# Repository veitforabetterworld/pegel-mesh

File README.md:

# pegel-mesh

Wasserstände von entfernten Pegeln per Funk ins Netz, ohne Mobilfunk. Ein Sender am Fluss liest die Pegelsonde (RS485) und funkt über [MeshCore](https://github.com/meshcore-dev/MeshCore) (868 MHz) zu einem Empfänger mit WLAN, der die Werte an die **hochwasserdienst**-API schickt. Der Sender läuft mit Solarpanel und Akku.

Zwei Trägerplatinen, eine Firmware (gleiche XIAO-Pins; die Firmware erkennt den Akku selbst):

| Platine | Akku | Versorgung |
|---|---|---|
| [`pegel-sender-12v`](hardware/pegel-sender-12v/README.md) (100 × 70 mm) | LiFePO4 oder ohne | Solarpanel 12-V-Klasse oder 12-V-Netzteil |
| [`pegel-sender-5v`](hardware/pegel-sender-5v/README.md) (58 × 46 mm) | Li-Ionen oder ohne | USB-C-Netzteil oder USB-C-Solarpanel (5 V), Heizung 1,7 W |
| [`pegel-stapel`](hardware/pegel-stapel/README.md) (Stapel) | wie oben | RS485-Platine auf Ladeplatine 5 V (beide 21 × 17,8 mm, wie der XIAO) oder 12 V (100 × 70 mm); Thermolader für 12-V-Netzteil und 12-V-Solar im Entwurf, noch unverdrahtet |

## Platine (12 V)

Die SMD-Teile bestückt JLCPCB (Dateien in [`hardware/pegel-sender-12v/fab/`](hardware/pegel-sender-12v/fab/)). Selbst löten:

| Teil | Wert | Beispiel |
|---|---|---|
| SOLAR/12V, AKKU | Schraubklemme 2-pol., Raster 5,08 mm | Phoenix MKDS 1,5/2-5,08 |
| SONDE, HEIZ/NTC | Schraubklemme 4-pol., Raster 5,08 mm | Phoenix MKDS 1,5/4-5,08 |
| L1 | Spule 15 µH, ≥ 0,9 A, radial Ø 7 mm, Raster 3 mm | Bourns RLB0712-150KL |
| L2 | Spule 10 µH, ≥ 0,5 A, radial Ø 7 mm, Raster 3 mm | Bourns RLB0712-100KL |
| C22 | Elko 220 µF 16 V, Polymer oder Low-ESR, Ø 8 mm, Raster 3,5 mm | Panasonic 16SEPF220M |
| C23 | Elko 220 µF 50 V, Low-ESR, Ø 10 mm, Raster 5 mm | Panasonic EEU-FR1H221 |
| XIAO | 2× Buchsenleiste 1×7, 2,54 mm | |
| NETZTEIL | Stiftleiste 1×2, 2,54 mm + Steckbrücke | |

Elkos: Plus an das Pad mit „+“.

Schaltplan: [`hardware/pegel-sender-12v/preview/`](hardware/pegel-sender-12v/preview/) (Blockschaltbild und ein Blatt je Funktionsblock), Technik in [`hardware/pegel-sender-12v/`](hardware/pegel-sender-12v/README.md).

## Anschlüsse

| Klemme | Was |
|---|---|
| **SOLAR/12V** | 12-V-Solarpanel (Leerlauf ≤ 25 V; 10 W Flachland, 30 W Mittelgebirge) **oder** 12-V-Netzteil |
| **AKKU** | LiFePO4, **1 Zelle** (3,2 V), z. B. 2–3 × 6 Ah parallel. Rückstellende Sicherung **RUEF300** (Littelfuse PolySwitch, hält 3 A, löst bei 6 A aus) im Pluskabel, direkt am Akku-Pluspol |
| **HEIZ/NTC** | H+ / H−: Heizwiderstand 68 Ω 10 W; NTC / NTC: Fühler 10 kΩ B3950, **auf den Akku** kleben |
| **SONDE** | V+ rot, V− schwarz, A weiß, B blau. RS485 Modbus RTU, 9600 8N1, Adresse 1, 12 V ≤ 30 mA |
| **NETZTEIL** (Brücke) | gesteckt bei Netzteil, offen bei Solarpanel |

Ohne NTC lädt der Sender nie (gilt als Frost). XIAO nRF52840 mit Wio-SX1262 aufstecken, USB zum Platinenrand („USB ->“); den BAT-Anschluss am XIAO nicht benutzen.

## Installation

Voraussetzungen: Git, Python 3.12+, USB-Treiber für die XIAO-Boards.

```bash
git clone https://github.com/veitforabetterworld/pegel-mesh.git
```

```bash
cd pegel-mesh && git submodule update --init
```

```bash
python3 -m pip install platformio cryptography
```

```bash
python3 tools/genkeys.py
```

`genkeys.py` legt `secrets/` an (nicht im Repo, sicher aufbewahren). Dort von Hand ausfüllen: **`secrets/receiver_wifi.h`** mit WLAN, API-Key (hochwasserdienst: Admin > API-Keys) und Name/Koordinaten der Stationen. Weitere Sender: `python3 tools/genkeys.py A B C`.

Flashen (Port anpassen, unter Windows z. B. `COM5`):

```bash
python3 tools/pio.py run -e pegel_sender_a -t upload --upload-port /dev/ttyACM0
```

| Umgebung | Gerät |
|---|---|
| `pegel_sender_a` | Sender, Messung jede Minute |
| `pegel_sender_b` | Sender, Messung alle 5 min |
| `pegel_receiver` | Empfänger, XIAO ESP32-S3 + Wio-SX1262 |

Immer `tools/pio.py` statt `pio` aufrufen; es hängt `pegel.ini` in das MeshCore-Submodul ein.

## Funkausfall und Nachsenden

Der Sender hält jede Messung, bis der Empfänger sie quittiert: 6144 Messungen, bei Sender A gut 4 Tage, bei Sender B gut 3 Wochen. Ist der Puffer voll, fällt die älteste Messung heraus; nach 30 Tagen verfällt eine Messung ebenfalls. Bei gestörter Verbindung stehen die Messungen zusätzlich im Flash und überstehen Stromausfall und Neustart; die Uhrzeit dafür kommt mit jeder Quittung vom Empfänger.

- Im Messtakt geht immer ein Block mit den neuesten Messungen raus (bis 75 je Paket). Bleibt die Quittung aus, versucht es der Sender erst im nächsten Messtakt wieder.
- Kam die Quittung, folgt der restliche Stau Block für Block, neueste zuerst, solange das Sendebudget von 1 % je Stunde reicht (MeshCore setzt es durch). Ein Tag Ausfall von Sender A ist so in knapp einer Stunde nachgeholt.
- Daten und Quittungen laufen nur auf dem bekannten Pfad oder ohne Hops, nie geflutet.

Fängt der Zähler eines Senders neu an (Tausch, Neuaufsetzen), übernimmt der Empfänger den neuen Stand nach etwa 30 Blöcken; sofort geht es am Empfänger über USB-Serial mit `creset <Sender>`, z. B. `creset A`.

## Langzeitbetrieb

Die Firmware ist für den Betrieb über viele Jahrzehnte ausgelegt (Watchdog, Überlauf- und Verschleißschutz). Der Empfänger nimmt die Uhrzeit vom Server. Zwischen den Messungen schlafen Funkchip und CPU. Bei gestörter Verbindung schreibt der Sender jede Messung mit Uhrzeit in den Flash: nach einem Stromausfall sendet er sie mit dem richtigen Zeitstempel nach.

Notfallwege testen: Builds `pegel_sender_a_test` und `pegel_receiver_test` (Serial-Befehle in `firmware/sender/main.cpp` bzw. `firmware/receiver/main.cpp`, `PEGEL_TEST_CMDS`).

## GPS-Tracker

Der Empfänger ist zugleich Gateway für GPS-Tracker: XIAO nRF54LM20A Sense + Wio-SX1262 + L76K-GNSS-Modul (Seeed 109100021). Der Tracker schläft zwischen den Ortungen in System OFF, meldet Position und Akkustand verschlüsselt über MeshCore, speichert nicht quittierte Meldungen zwischen und reicht sie nach. Bei eingeschaltetem Bewegungsalarm weckt ihn der Bewegungssensor. Der Empfänger lädt die Meldungen zu [tracker.plenivo.de](https://tracker.plenivo.de) hoch und gibt dem Tracker dessen Einstellungen (Intervall, Alarm) mit. Firmware in [`firmware/tracker/`](firmware/tracker/), Paketformat in [`firmware/common/tracker_packet.h`](firmware/common/tracker_packet.h).

Schlüssel für einen neuen Tracker (hier `T1`), danach den Empfänger neu flashen:

```bash
python3 tools/genkeys.py --tracker T1
```

In `secrets/receiver_wifi.h` `TRACKER_API_URL` (`https://tracker.plenivo.de/api`) und je Tracker den API-Key aus dem Tracker-Dialog der Webseite eintragen. Ohne URL gibt der Empfänger die Meldungen nur auf Serial aus; Einstellungen lassen sich dann mit `tset <tracker> <intervall 0..3> <alarm 0..3> <alarmintervall 0..3>` auf Serial setzen.

Der nRF54LM20A wird von MeshCore noch nicht offiziell unterstützt; der Tracker baut gegen das Submodul `MeshCore-nrf54` (MeshCore-PR #3530). `tools/pio.py` wählt es für alle Umgebungen `tracker_*` und hängt `tracker.ini` ein.

```bash
python3 tools/pio.py run -e tracker_t1 -t upload
```

Ein neues Board ist ab Werk gesperrt (APPROTECT): einmal mit OpenOCD über den CTRL-AP löschen und dann `-t bootloader` (Bootloader, SoftDevice, Firmware) flashen; danach reicht `-t upload`. Die USB-Seriell-Brücke des Boards bleibt nach System OFF oft hängen; das Log liegt deshalb zusätzlich im RAM und lässt sich per SWD lesen (weckt den Tracker dabei auf):

```bash
bash tools/tracker_log.sh
```

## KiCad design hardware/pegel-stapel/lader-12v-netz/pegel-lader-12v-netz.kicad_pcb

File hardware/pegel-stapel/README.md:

# pegel-stapel: Ladeplatine + RS485-Platine zum Stapeln

Die Sender-Elektronik in zwei Platinen, gestapelt wie der XIAO selbst. Unten liegt eine Ladeplatine, wahlweise für 5 V oder 12 V. Darüber sitzt die RS485-Platine, ganz oben XIAO nRF52840 + Wio-SX1262. Alle Platinen haben die XIAO-Leisten an derselben Stelle, und die Signale laufen durch die Stapelbuchsen. Firmware: die normalen Umgebungen `pegel_sender_a`/`_b`; den Akku (Li-Ionen oder LiFePO4) erkennt sie selbst, von der Temperaturregelung weiß sie nichts.

| Platine | Inhalt | Größe |
|---|---|---|
| [`rs485/`](rs485/) | 12 V für die Sonde (TPS61040, ausgelegt auf 13 mA), RS485 (SP3485), Lötstellen J3 **A, B, GND, 12V**, durchkontaktiert im 2,54-mm-Raster | 20,955 × 17,78 mm (Umriss des XIAO) |
| [`lader-5v/`](lader-5v/) | **Thermolader 5 V:** 5-V-Eingang J1, NTC J4, LM393: unter ~2,5 °C Heizung 5 × 300 Ω (0,42 W), über ~42 °C Laden aus, dazwischen Laden über den XIAO | 20,955 × 17,78 mm (Umriss des XIAO) |
| [`lader-12v-netz/`](lader-12v-netz/) | **Thermolader 12 V Netzteil** (9–15 V): TPS54331 auf 4,88 V, dahinter wie 5 V. Verdrahtet, GND und Versorgung als Flächen | 21,975 × 17,78 mm |
| [`lader-12v-solar/`](lader-12v-solar/) | **Thermolader 12 V Solar** (36 Zellen, Leerlauf bis 25 V): TPS5430 auf 4,92 V mit Panelregelung, dahinter wie 5 V. Noch nicht verdrahtet | 31,455 × 17,78 mm |
| [`lader-12v/`](lader-12v/) | Solar/12 V, LiFePO4-Lader, Frostschutz, Schaltung, Klemmen und Bohrungen wie `pegel-sender-12v` (gleiches Gehäuse) | 100 × 70 mm |

| | |
|---|---|
|  |  |

## Stapel

- **Stapelmaß:** Die XIAO-Leisten liegen auf allen Platinen gleich, 15,24 mm auseinander, USB-C nach rechts ([`tools/stack.py`](tools/stack.py)). RS485-Platine und Thermolader haben den Umriss des XIAO und keine Bohrungen, das Langloch-Symbol unten zeigt die USB-C-Kante. Die 12-V-Ladeplatine hat nur die vier Gehäusebohrungen in den Ecken.
- **Ladeplatine:** zwei Buchsenleisten 1×7 (8,5 mm).
- **RS485-Platine:** zwei Stapel-Buchsenleisten 1×7 mit langen Stiften. Die Stifte gehen nach unten in die Ladeplatine, der XIAO steckt oben.
- **5-V-Ladeplatine (Thermolader 5 V):** nur so groß wie der XIAO, ohne Bohrungen; sie hängt an den beiden Leisten. Das Langloch-Symbol auf der Unterseite zeigt, an welcher Kante die USB-C-Buchse des XIAO sitzt.
- **Halt:** Die Platinen halten nur an den Leisten, Abstandsbolzen gibt es nicht.
- **Signale zwischen den Platinen:** nur über die 14 Pins der XIAO-Leisten, nämlich D0 (Sonde ein), D6/D7 (RS485), 3V3, GND und 5V. Keine Drähte.
- **Frostschutz in Hardware, beide Ladeplatinen:** ein NTC 10 kΩ B3950 am Akku.
  - 5 V: Eine Hälfte des LM393 trennt unter ~2,5 °C den Lader des XIAO vom 5-V-Eingang (Q2) und heizt, bis der Akku wieder ~4,6 °C hat. Die andere trennt über ~42 °C (ungünstigste Toleranzen 39,2–44,8 °C) bis ~37 °C (Q3). Ohne NTC: kein Laden, Heizung an. NTC-Kurzschluss: kein Laden, Heizung aus.
  - 12 V: Ein LM324 regelt wie bei `pegel-sender-12v`.

## Versorgung

- **Sonde:** Der 12-V-Wandler läuft aus dem **3V3-Pin** des XIAO, nicht aus dem Akku. Bei 5 V liefert der Regler des XIAO die 3,3 V (SGM2040: 280 mA garantiert, höchstens 10 µF am Ausgang empfohlen). Bei 12 V speist die Ladeplatine den 3V3-Pin über D10 direkt aus dem LiFePO4-Akku. Die Sonde braucht 13 mA bei 12 V, das sind ~61 mA aus 3,3 V und nur während der Messung.
- **Einschalten der Sonde:** Q7 schaltet Wandler und SP3485 gemeinsam. C9/C11 rampen die 3,3 V, C10/D7/R19 die 12 V (~65 ms, zählt zur Vorlaufzeit von 2 s). Gerechnet mit den ungünstigsten Grenzen bleibt 3V3 bis 100 µF in der Sonde über 3,1 V, bei 220 µF 2,6 V. Am ersten Aufbau mit echter Sonde messen.
- **Sondenkabel:** Eine 1 hält auf dem Bus nur die Vorspannung R17/R18 (1 kΩ). Bei 9600 Bd reicht das rechnerisch für ~180 m (120 pF/m). Kein Abschlusswiderstand nötig.
- **5 V:** Li-Ionen-Akku an die BAT-Pads des XIAO und unter die Ladeplatine kleben, mit den Heizwiderständen darüber. Der NTC kommt an den Akku. J4 (NTC) und J1 (5 V) sind Lötpads auf der Unterseite. Stiftenden kürzen und samt Pads gegen den Akku isolieren.
- **Wärme:** nachgerechnet in [`verify/report/thermal.md`](verify/report/thermal.md) (700 mAh, 3 cm Styropor). Die Heizung reicht bis etwa −25 °C, bei 4,5 V bis etwa −19 °C. **Fällt der NTC ab, heizt sie dauernd:** der Akku kommt bei 20 °C Außenluft auf ~50 °C, bei 35 °C auf ~64 °C (61–69 °C); über seine 60 °C kommt er ab ~31 °C Außenluft (ungünstig ab 26 °C). Die Hitzeabschaltung verhindert das nicht, sie schaltet nur das Laden. NTC deshalb sicher am Akku befestigen, neben der Platine, nie zwischen Platine und Akku: dort lädt es bei teils gefrorenem Akku. Ab ~35 °C Außenluft lädt es nur zeitweise, über ~40 °C gar nicht.
- **Kupfer (5 V):** GND beidseitig als Fläche ohne GND-Bahnen, V5, HEAT_N und XIAO_5V als Flächen, Signale 0,3 mm, übrige Versorgung 0,6 mm, Abstand ≥ 0,2 mm. Nach Änderungen in KiCad Flächen neu füllen (Taste B).
- **Kupfer (RS485):** GND beidseitig als Fläche, V3_SW und Schaltknoten als Flächen, Signale 0,3 mm, 12 V und XIAO-3V3 im Hauptweg 0,6–0,8 mm. Alle Vias 0,6/0,3 mm, mindestens 0,15 mm neben dem eigenen und 0,2 mm neben fremden SMD-Pads. Engste Versorgungsstelle: V3_SW zwischen R16 und L1 mit 0,28 mm. Nach Änderungen in KiCad Flächen neu füllen (Taste B).
- **12 V:** Akku, Panel und Heizung/NTC wie bei `pegel-sender-12v` an J2, J1 und J4.

Alle SMD-Teile sind Basic oder Preferred bei JLCPCB, kein Extended: `python ../pegel-sender-12v/verify/jlc_parts.py rs485` usw.

## Bearbeiten und exportieren

Die `.kicad_pcb` sind die Originale. Lagen, Bahnen und Beschriftung macht man von Hand in KiCad, kein Skript platziert oder routet. `design.py` je Platine ist die Soll-Netzliste und die Stückliste; bei Änderungen an der Schaltung beides nachziehen.

Prüfen (DRC, Abgleich mit `design.py`), ohne etwas zu schreiben:

```bash
python tools/fab.py --check
```

Prüfen und Fertigungsdaten (`<platine>/fab/`) samt 3D-Bildern (`<platine>/preview/`) schreiben, einzelne Platine z. B. `python tools/fab.py lader-5v`:

```bash
python tools/fab.py
```

**Vor dem Bestellen, RS485-Platine:** Die Drehlage von Q6, Q8, D4, D5 und D7 im JLC-Viewer prüfen. L1 (LCSC C45403) wird von JLCPCB bestückt.

**Offen, 12-V-Thermolader:** Netzteil: verdrahtet, 21,975 mm lang, GND beidseitig als Fläche ohne GND-Bahnen (mind. 0,3 mm breit; Rückstrompfade Eingang, Wandler und XIAO mind. 0,89 mm, Ausgangskondensator C7 zum XIAO 0,4 mm; VIN_RAW- und GND-Via sitzen in den Drahtpads J1.1/J1.2), Heizreihen (V5, HEAT_N) und Schaltknoten als Flächen, Signale 0,3 mm, Versorgung 0,6 mm, Ecken R 1,5 mm (stehen an den Ecken bis 0,17 mm über den XIAO). Solar: Teile wie am 5-V-Lader, der Wandler links von x = 0, noch ohne Leiterbahnen; `fab.py` exportiert erst nach dem Verdrahten. Gegenüber dem 5-V-Lader kleinere Gehäuse, alle Basic/Preferred: R1, R3–R6, R8, R9 und C1, C2, C4 in 0402, die Heizung in 0805 (je 0,08 W von 0,125 W), C3 in 0805; am Netzteil ein 47-µF-Ausgangskondensator statt zwei 22 µF. L1 (LCSC C83472) von Hand löten. Wärme nachgerechnet in [`verify/report/thermal-12v.md`](verify/report/thermal-12v.md): Fällt der NTC ab, erreicht der Akku 60 °C schon ab ~21 °C Außenluft (Solar) bzw. ~28 °C (Netzteil), weil die Wandlerverluste dazukommen. Die 0805-Heizung liegt dann beim Solar-Lader ab ~38 °C Außenluft über ihrer Lastminderung. Der Lader des XIAO bricht nach 10 h ab (~1 Ah bei 100 mA).

LM393 (5 V) und LM324 (12 V) sind laut Datenblatt bis 0 °C spezifiziert. Gleichwertig bis −40 °C wäre der LM2903, aber Extended bei JLCPCB (Rüstgebühr ~3 USD).

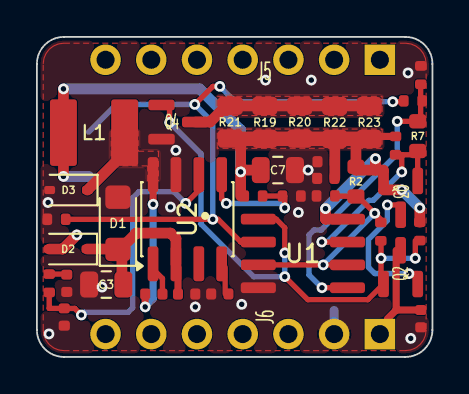
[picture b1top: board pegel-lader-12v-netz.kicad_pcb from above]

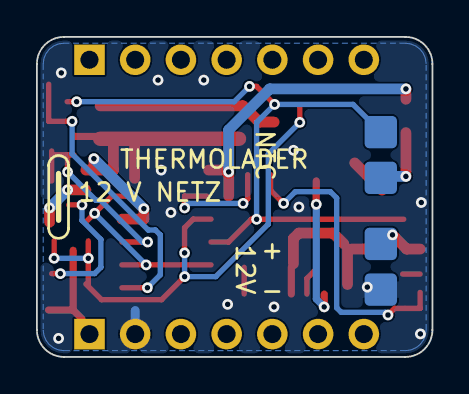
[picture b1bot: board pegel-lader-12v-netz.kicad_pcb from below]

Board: 2 copper layers, 22.0 x 17.8 mm, 40 parts (2 on the bottom side), 18 nets.

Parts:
C1, C4: 10uF 6.3V 0402; C_0402_1005Metric
C2, C5, C6: 100nF 50V 0402; C_0402_1005Metric
C3: 10uF 50V 0805; C_0805_2012Metric
C7: 47uF 6.3V 0805; C_0805_2012Metric
C9, C10: 10nF 0402; C_0402_1005Metric
C11: 47pF 0402; C_0402_1005Metric
D1: SMF15A; D_SMF
D2, D3: B5819WS; D_SOD-323
J1: 12V NETZTEIL; SolderPads_1x02_B_1.8x1.8mm_P2.54mm
J4: NTC; SolderPads_1x02_B_1.8x1.8mm_P2.54mm
J5: XIAO D0-D6; PinSocket_1x07_P2.54mm_Vertical
J6: XIAO 5V-D7; PinSocket_1x07_P2.54mm_Vertical
L1: 22uH; L_4030_HandSolder
Q2, Q3: AO3401A; SOT-23
Q4: AO3400A; SOT-23
R1, R3: 4.7k; R_0402_1005Metric
R2: 30k; R_0603_1608Metric
R4: 100k; R_0402_1005Metric
R5: 39k; R_0402_1005Metric
R6: 300k; R_0402_1005Metric
R7: 2M; R_0603_1608Metric
R8, R9, R11: 10k; R_0402_1005Metric
R10: 51k; R_0402_1005Metric
R12: 8.2k; R_0402_1005Metric
R19, R20, R21, R22, R23: 300; R_0805_2012Metric
U1: LM393; SOIC-8_3.9x4.9mm_P1.27mm
U2: TPS54331; SOIC-8_3.9x4.9mm_P1.27mm

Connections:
BUCK_BOOT: C6.1, U2.1
BUCK_COMP: C11.1, R12.1, U2.6
BUCK_FB: R10.2, R11.1, U2.5
BUCK_SS: C9.1, U2.4
BUCK_SW: C6.2, D3.1, L1.1, U2.8
COLD: Q2.1, Q4.1, R6.1, R8.2, U1.1
COMP_RC: C10.1, R12.2
GND: C1.2, C2.2, C3.2, C4.2, C5.2, C7.2, C9.2, C10.2, C11.2, D1.2, D3.2, J1.2, J6.2, Q4.2, R1.2, R3.2, R5.1, R11.2, U1.4, U2.7
HEAT_N: Q4.3, R19.2, R20.2, R21.2, R22.2, R23.2
HOT: Q3.1, R7.1, R9.2, U1.7
T_COLD: R2.2, R3.1, R6.2, U1.3, U1.6
T_HOT: R4.2, R5.2, R7.2, U1.5
T_NTC: J4.2, R1.1, R4.1, U1.2
V5: C1.1, C2.1, C7.1, J4.1, L1.2, Q3.2, R2.1, R8.1, R9.1, R10.1, R19.1, R20.1, R21.1, R22.1, R23.1, U1.8
V5_CHG: Q2.2, Q3.3
VIN: C3.1, C5.1, D1.1, D2.1, U2.2
VIN_RAW: D2.2, J1.1
XIAO_5V: C4.1, J6.1, Q2.3

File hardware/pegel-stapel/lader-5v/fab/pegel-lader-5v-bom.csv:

Comment,Designator,Footprint,LCSC Part #
AO3401A,"Q1,Q3,Q2",SOT-23,C15127
SMAJ5.0A,D1,D_SMA,C19077523
10uF 10V,"C1,C4",R_0603_1608Metric,C19702
LM393,U1,SOIC-8_3.9x4.9mm_P1.27mm,C7955
100nF,C2,R_0603_1608Metric,C14663
4.7k,"R1,R3",R_0603_1608Metric,C23162
30k,R2,R_0603_1608Metric,C22984
300k,R6,R_0603_1608Metric,C23024
10k,"R8,R9",R_0603_1608Metric,C25804
100k,R4,R_0603_1608Metric,C25803
39k,R5,R_0603_1608Metric,C23153
2M,R7,R_0603_1608Metric,C22976
AO3400A,Q4,SOT-23,C20917
300,"R19,R20,R21,R22,R23",R_1206_3216Metric,C17887

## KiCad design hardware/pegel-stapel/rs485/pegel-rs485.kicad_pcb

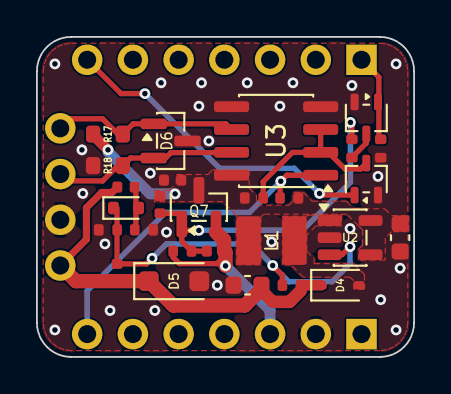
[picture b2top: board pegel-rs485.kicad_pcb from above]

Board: 2 copper layers, 21.0 x 17.8 mm, 30 parts (0 on the bottom side), 15 nets.

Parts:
C3: 22pF 0402; C_0402_1005Metric
C4: 10uF 25V 0603; C_0603_1608Metric
C5: 10uF 10V; C_0603_1608Metric
C6: 100nF 0402; C_0402_1005Metric
C9: 220nF 0402; C_0402_1005Metric
C10, C11: 1uF 25V 0402; C_0402_1005Metric
D4: 1N5819WS; D_SOD-323
D5: SMF15A; D_SOD-123F
D6: PSM712; SOT-23
D7: 1N4148WT; D_SOD-523
J3: SONDE; WirePads_1x04_P2.54mm_D1.0mm
J5: XIAO D0-D6; PinSocket_1x07_P2.54mm_Vertical
J6: XIAO 5V-D7; PinSocket_1x07_P2.54mm_Vertical
L1: 10uH; L_3015_HandSolder
Q6, Q8: BSS138W; SOT-323_SC-70
Q7: AO3401A; SOT-23
R9: 510k; R_0402_1005Metric
R10: 56k; R_0402_1005Metric
R11, R13, R15, R16: 10k; R_0402_1005Metric
R14, R19: 100k; R_0402_1005Metric
R17, R18: 1k; R_0603_1608Metric
U2: TPS61040; SOT-23-5
U3: SP3485EN; SOIC-8_3.9x4.9mm_P1.27mm

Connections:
BST_FB: C3.2, D7.1, R9.2, R10.1, U2.3
BST_SW: D4.2, L1.2, U2.1
GND: C4.2, C5.2, C6.2, D5.2, D6.3, J3.3, J6.2, Q6.2, Q8.2, R10.2, R11.2, R18.1, R19.2, U2.2, U3.4, U3.5
PSW_G: C9.1, C11.2, Q7.1, R13.1, R14.2
PSW_PD: Q6.3, R13.2
RS485_A: D6.1, J3.1, R17.2, U3.6
RS485_B: D6.2, J3.2, R18.2, U3.7
RS_DE: Q8.3, R15.2, U3.2, U3.3
SENS_EN: J5.1, Q6.1, R11.1
SS: C10.2, D7.2, R19.1
UART_RX: J6.7, R16.2, U3.1
UART_TX: J5.7, Q8.1
V3_SW: C5.1, C6.1, C9.2, L1.1, Q7.3, R15.1, R16.1, R17.1, U2.4, U2.5, U3.8
V12_PROBE: C3.1, C4.1, C10.1, D4.1, D5.1, J3.4, R9.1
XIAO_3V3: C11.1, J6.3, Q7.2, R14.1

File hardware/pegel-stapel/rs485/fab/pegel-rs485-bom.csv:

Comment,Designator,Footprint,LCSC Part #
AO3401A,Q7,SOT-23,C15127
100k,"R14,R19",R_0402_1005Metric,C25741
220nF 0402,C9,C_0402_1005Metric,C16772
1uF 25V 0402,"C11,C10",C_0402_1005Metric,C52923
BSS138W,"Q6,Q8",SOT-323_SC-70,C28646265
10k,"R11,R13,R15,R16",R_0402_1005Metric,C25744
TPS61040,U2,SOT-23-5,C7722
10uH,L1,L_3015_HandSolder,C45403
1N5819WS,D4,D_SOD-323,C191023
10uF 10V,C5,C_0603_1608Metric,C19702
10uF 25V 0603,C4,C_0603_1608Metric,C96446
510k,R9,R_0402_1005Metric,C11616
56k,R10,R_0402_1005Metric,C25796
22pF 0402,C3,C_0402_1005Metric,C1555
1N4148WT,D7,D_SOD-523,C7420320
SMF15A,D5,D_SOD-123F,C19077509
SP3485EN,U3,SOIC-8_3.9x4.9mm_P1.27mm,C8963
100nF 0402,C6,C_0402_1005Metric,C1525
1k,"R17,R18",R_0603_1608Metric,C21190
PSM712,D6,SOT-23,C32677

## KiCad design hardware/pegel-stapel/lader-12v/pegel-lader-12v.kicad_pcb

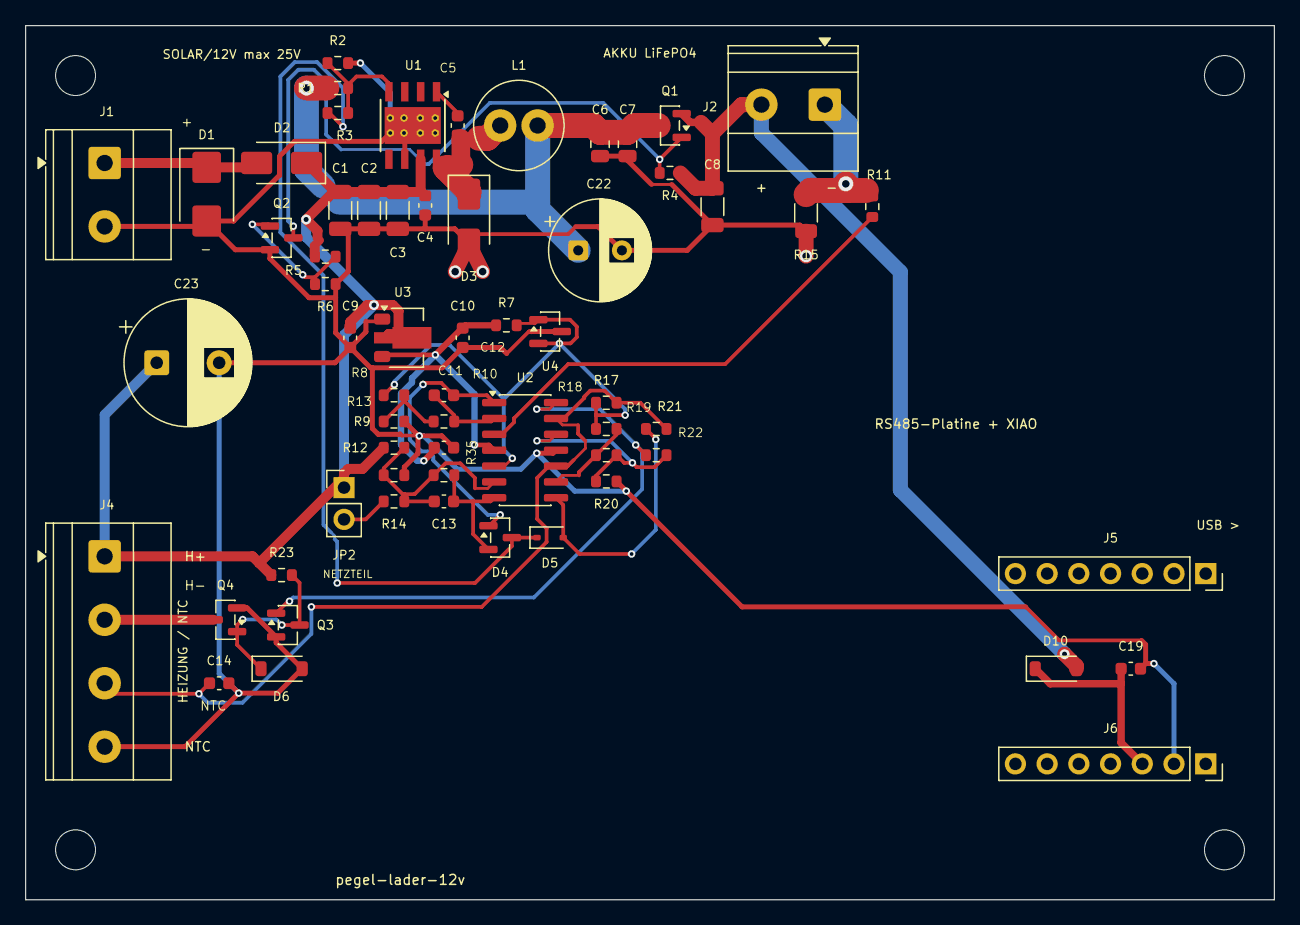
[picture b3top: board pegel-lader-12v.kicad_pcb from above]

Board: 2 copper layers, 100.0 x 70.0 mm, 66 parts (0 on the bottom side), 29 nets.

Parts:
C1, C2, C3: 10uF 50V; C_1206_3216Metric
C4, C11, C12, C14: 100nF; C_0603_1608Metric
C5: 10nF; C_0603_1608Metric
C6, C7: 22uF 25V; C_0805_2012Metric
C8: 100uF 6.3V; C_1206_3216Metric
C9, C10: 1uF; C_0603_1608Metric
C13: 100pF; C_0603_1608Metric
C19: 10uF 10V; C_0603_1608Metric
C22: 220uF 16V; CP_Radial_D8.0mm_P3.50mm
C23: 220uF 50V; CP_Radial_D10.0mm_P5.00mm
D1: SMBJ28A; D_SMB
D2, D3: SS34; D_SMA
D4: BAV70; SOT-23
D5: 1N4148WS; D_SOD-323
D6: 10V; D_SOD-123
D10: B5819W; D_SOD-123
H4, H5, H6, H7: M3; MountingHole_3.2mm_M3
J1: SOLAR / 12V; TerminalBlock_Phoenix_MKDS-1,5-2-5.08_1x02_P5.08mm_Horizont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
J2: AKKU 3,2V; TerminalBlock_Phoenix_MKDS-1,5-2-5.08_1x02_P5.08mm_Horizont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
J4: HEIZ NTC; TerminalBlock_Phoenix_MKDS-1,5-4-5.08_1x04_P5.08mm_Horizont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
J5: XIAO D0-D6; PinSocket_1x07_P2.54mm_Vertical
J6: XIAO 5V-D7; PinSocket_1x07_P2.54mm_Vertical
JP2: NETZTEIL; PinHeader_1x02_P2.54mm_Vertical
L1: 15uH; L_Radial_D7.0mm_P3.00mm
Q1: AO3401A; SOT-23
Q2, Q3: 2N7002; SOT-23
Q4: HL2310A; SOT-23
R1: 56k; R_0603_1608Metric
R2: 30k; R_0603_1608Metric
R3, R10: 10k; R_0603_1608Metric
R4, R5, R23: 100k; R_0603_1608Metric
R6, R18: 47k; R_0603_1608Metric
R7, R9, R11: 1k; R_0603_1608Metric
R8, R20: 49.9k; R_0603_1608Metric
R12, R14: 300k; R_0603_1608Metric
R13: 51k; R_0603_1608Metric
R15: 0.1; R_1206_3216Metric
R17: 27k; R_0603_1608Metric
R19: 5.1k; R_0603_1608Metric
R21, R35: 1M; R_0603_1608Metric
R22: 2M; R_0603_1608Metric
U1: TPS5430; TI_SO-PowerPAD-8_ThermalVias
U2: LM324; SOIC-14_3.9x8.7mm_P1.27mm
U3: HT7550-1; SOT-89-3
U4: CJ431; SOT-23

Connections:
+5V: C10.1, C11.1, R7.1, U2.4, U3.3
BAT_N: J2.1, R11.1, R15.1
CC_INT: C12.1, R10.2, U2.2
CC_OUT: C12.2, D4.1, U2.1
CC_SENSE: R11.2, U2.3
CC_SET: R8.2, R9.1, R10.1
CHG_BOOT: C5.1, U1.1
CHG_FB: R1.2, R2.1, R3.2, U1.4
CHG_INH: D5.2, R21.1, U2.8
CHG_LIM: D4.3, D5.1, R3.1
CHG_OUT: C6.1, C7.1, C22.1, L1.2, Q1.3, R1.1
CHG_PG: Q1.1, Q2.3, R4.1
CHG_PGD: Q2.1, R5.2, R6.1
CHG_SW: C5.2, D3.1, L1.1, U1.8
GND: C1.2, C2.2, C3.2, C4.2, C6.2, C7.2, C8.2, C9.2, C10.2, C11.2, C14.2, C19.2, C22.2, C23.2, D1.2, D3.2, D6.2, J1.2, J4.4, J6.2, Q2.2, Q3.2, Q4.2, R2.2, R6.2, R9.2, R13.2, R15.2, R20.2, U1.6, U1.9, U2.11, U3.1, U4.3
HEAT_G: D6.1, Q3.3, Q4.1, R23.2
HEAT_N: J4.2, Q4.3
HEAT_OFF: Q3.1, R22.1, U2.14
IN_RAW: D1.1, D2.2, J1.1
T_NTC: C14.1, J4.3, R17.2, R21.2, U2.10, U2.13
T_REF0: R18.2, R19.1, U2.9
T_REF2: R19.2, R20.1, R22.2, U2.12
VIN_DIV: C13.1, R12.2, R13.1, R14.2, R35.1, U2.6
VIN_J: JP2.2, R14.1
VIN_OUT: C13.2, D4.2, R35.2, U2.7
VREF: R7.2, R8.1, R17.1, R18.1, U2.5, U4.1, U4.2
VSOL: C1.1, C2.1, C3.1, C4.1, C9.1, C23.1, D2.1, J4.1, JP2.1, R5.1, R12.1, R23.1, U1.7, U3.2
VSYS: C8.1, D10.2, J2.2, Q1.2, R4.2
XIAO_3V3: C19.1, D10.1, J6.3

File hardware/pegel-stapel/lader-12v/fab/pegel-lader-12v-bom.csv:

Comment,Designator,Footprint,LCSC Part #
SMBJ28A,D1,D_SMB,C19077582
SS34,"D2,D3",D_SMA,C8678
10uF 50V,"C1,C2,C3",C_1206_3216Metric,C13585
TPS5430,U1,TI_SO-PowerPAD-8_ThermalVias,C9864
100nF,"C4,C11,C12,C14",C_0603_1608Metric,C14663
10nF,C5,C_0603_1608Metric,C57112
22uF 25V,"C6,C7",C_0805_2012Metric,C45783
56k,R1,R_0603_1608Metric,C23206
30k,R2,R_0603_1608Metric,C22984
10k,"R3,R10",R_0603_1608Metric,C25804
AO3401A,Q1,SOT-23,C15127
100k,"R4,R5,R23",R_0603_1608Metric,C25803
2N7002,"Q2,Q3",SOT-23,C8545
47k,"R6,R18",R_0603_1608Metric,C25819
100uF 6.3V,C8,C_1206_3216Metric,C15008
HT7550-1,U3,SOT-89-3,C16106
1uF,"C9,C10",C_0603_1608Metric,C15849
LM324,U2,SOIC-14_3.9x8.7mm_P1.27mm,C71035
CJ431,U4,SOT-23,C3113
1k,"R7,R9,R11",R_0603_1608Metric,C21190
49.9k,"R8,R20",R_0603_1608Metric,C23184
300k,"R12,R14",R_0603_1608Metric,C23024
51k,R13,R_0603_1608Metric,C23196
1M,"R35,R21",R_0603_1608Metric,C22935
100pF,C13,C_0603_1608Metric,C14858
BAV70,D4,SOT-23,C68978
1N4148WS,D5,D_SOD-323,C2128
0.1,R15,R_1206_3216Metric,C25334
27k,R17,R_0603_1608Metric,C22967
5.1k,R19,R_0603_1608Metric,C23186
2M,R22,R_0603_1608Metric,C22976
10V,D6,D_SOD-123,C19077408
HL2310A,Q4,SOT-23,C7420347
B5819W,D10,D_SOD-123,C8598
10uF 10V,C19,C_0603_1608Metric,C19702

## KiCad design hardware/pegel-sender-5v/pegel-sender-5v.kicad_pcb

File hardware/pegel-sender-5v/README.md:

# pegel-sender-5v

**58 × 46 mm**, abgerundete Ecken, **M3 in allen vier Ecken**. **J1** 5 V (+/−). **J3** Sonde: **A, B, GND, 12 V** (Pin 4 = V12_PROBE).  
Laden nur über **BQ25101 auf dem XIAO**. **Q10** legt V5 an J6 Pin 1. **Q9** schaltet 8× 120 Ω (1,7 W an 5 V) dagegen: Heizen und Laden schließen sich aus. **TP1** mit einem Draht an **P0.09 / NFC1** auf der Rückseite des XIAO. Die Firmware schaltet dieses Pad beim ersten Start auf GPIO (UICR, einmal Reset). Unter 5 °C Heizung, ab 8 °C Laden. Kein J8, keine BAT-Pads auf der Platine; **L1/VBAT** an **BAT+** des XIAO löten.

## Firmware

`env:pegel_sender_5v_*` in `pegel.ini` (`PEGEL_5V_BOARD=1`). `pegel_5v_power` liest die nRF-Die-Temperatur und treibt P0.09.

## XIAO

Zwei **1×7**-Buchsen, **15,24 mm** Abstand (Seeed). Module **von unten**. 3D-Vorschau: `render_preview.py` (WXR-Modelle unter `models/`).

## Erzeugen

`python3 relayout.py` → `layout.py` (offen für KiCad). `design.py` = Netzliste.

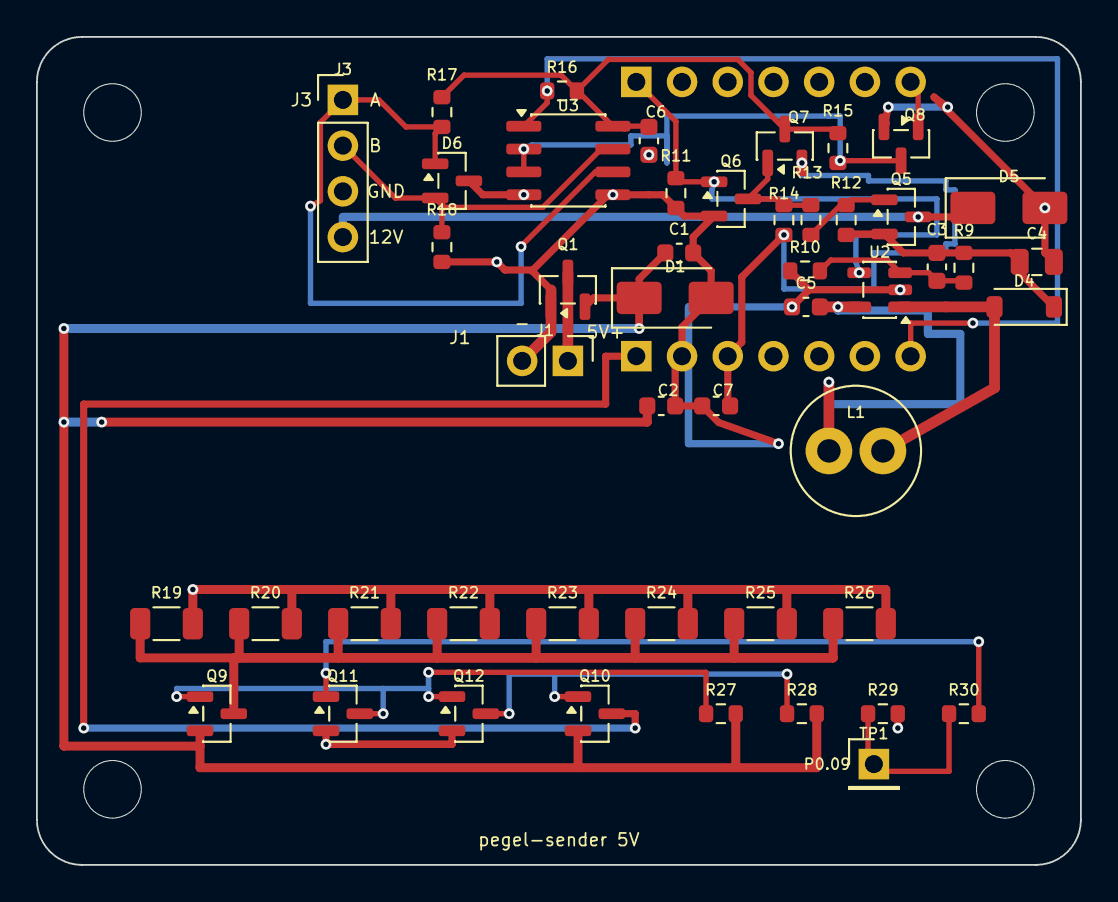
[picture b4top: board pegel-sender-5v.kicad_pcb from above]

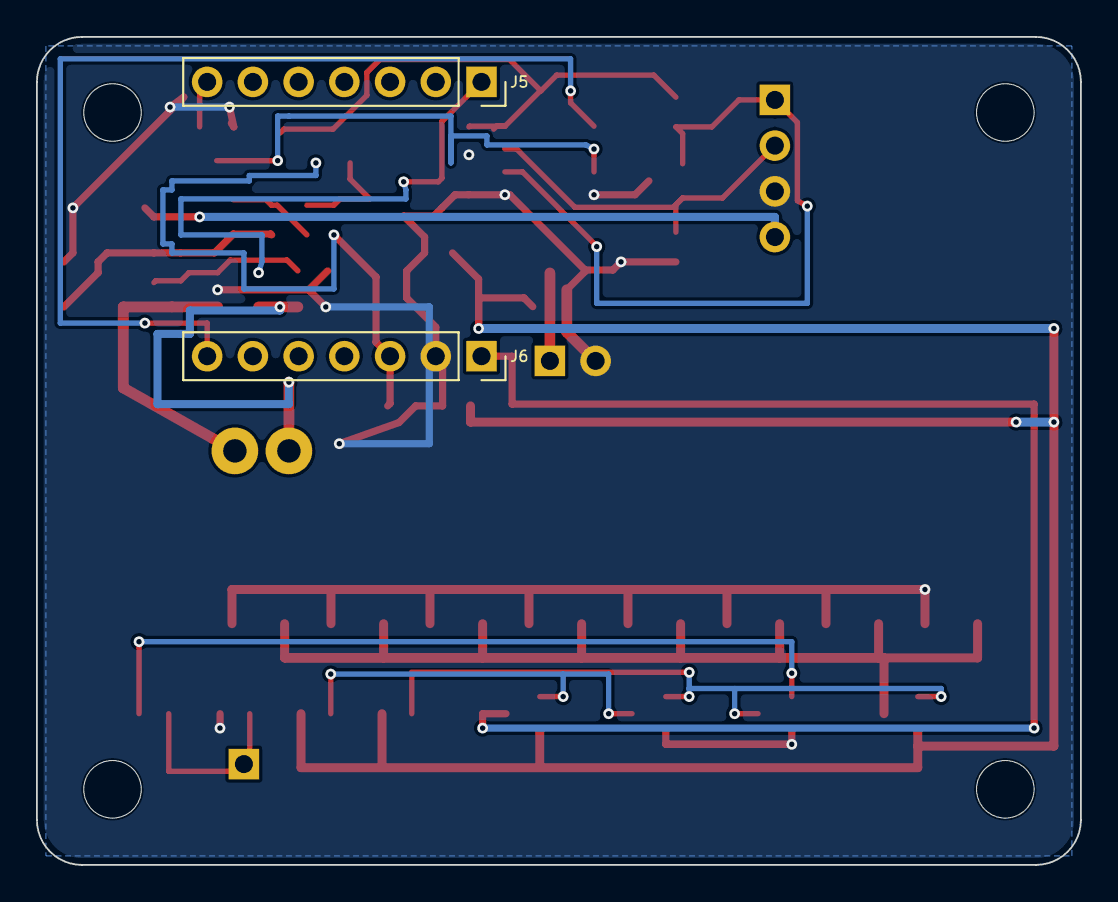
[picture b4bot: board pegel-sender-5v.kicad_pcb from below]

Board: 2 copper layers, 58.0 x 46.0 mm, 54 parts (2 on the bottom side), 24 nets.

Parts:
C1, C2, C5, C7: 10uF 10V; C_0603_1608Metric
C3: 22pF; C_0603_1608Metric
C4: 10uF 25V; C_0805_2012Metric
C6: 100nF; C_0603_1608Metric
D1: SMAJ5.0A; D_SMA
D4: B0540W; D_SOD-123
D5: SMAJ18A; D_SMA
D6: PSM712; SOT-23
H1, H2, H3, H4: M3; MountingHole_3.2mm_M3
J1: 5V IN; PinHeader_1x02_P2.54mm_Vertical
J3: SONDE; PinHeader_1x04_P2.54mm_Vertical
J5: XIAO D0-D6; PinSocket_1x07_P2.54mm_Vertical
J6: XIAO 5V-D10; PinSocket_1x07_P2.54mm_Vertical
L1: 10uH; L_Radial_D7.0mm_P3.00mm
Q1, Q5, Q7, Q9, Q10: AO3401A; SOT-23
Q6, Q8, Q11, Q12: 2N7002; SOT-23
R9: 510k; R_0603_1608Metric
R10: 56k; R_0603_1608Metric
R11, R12, R13, R14, R16, R27, R28, R29: 100k; R_0603_1608Metric
R15, R17, R18, R30: 10k; R_0603_1608Metric
R19, R20, R21, R22, R23, R24, R25, R26: 120; R_1206_3216Metric
TP1: P0.09; PinHeader_1x01_P2.54mm_Vertical
U2: TPS61040; SOT-23-5
U3: SP3485EN; SOIC-8_3.9x4.9mm_P1.27mm

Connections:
BST_FB: C3.2, R9.2, R10.1, U2.3
BST_SW: D4.2, L1.2, U2.1
GND: C1.2, C2.2, C4.2, C5.2, C6.2, C7.2, D1.2, D5.2, D6.3, J1.2, J3.3, J6.2, Q1.1, Q6.2, Q8.2, Q11.2, Q12.2, R10.2, R11.2, R18.2, R19.2, R20.2, R21.2, R22.2, R23.2, R24.2, R25.2, R26.2, R29.2, U2.2, U3.4, U3.5
HEAT: Q9.3, R19.1, R20.1, R21.1, R22.1, R23.1, R24.1, R25.1, R26.1
HEAT_EN: R29.1, R30.1, TP1.1
HEAT_GATE: Q11.1, R30.2
PSW_G: Q5.1, R12.2, R13.1
PSW_PD: Q6.3, Q7.1, R13.2, R14.2
QC_GATE: Q10.1, Q12.3, R28.1
QH_GATE: Q9.1, Q11.3, Q12.1, R27.1
RS485_A: D6.1, J3.1, R17.1, U3.6
RS485_B: D6.2, J3.2, R18.1, U3.7
RS_DE: Q8.3, R15.2, U3.2, U3.3
RS_VCC: C6.1, Q7.3, R15.1, R16.1, R17.2, U3.8
SENS_EN: J5.1, Q6.1, R11.1, U2.4
UART_RX: J6.7, R16.2, U3.1
UART_TX: J5.7, Q8.1
V5: C1.1, C2.1, D1.1, Q1.2, Q9.2, Q10.2, R27.2, R28.2
V12_PROBE: D5.1, J3.4, Q5.3
V12_RAW: C3.1, C4.1, D4.1, Q5.2, R9.1, R12.1
VBAT: C5.1, L1.1, U2.5
VIN_RAW: J1.1, Q1.3
XIAO_3V3: C7.1, J6.3, Q7.2, R14.1
XIAO_5V: J6.1, Q10.3

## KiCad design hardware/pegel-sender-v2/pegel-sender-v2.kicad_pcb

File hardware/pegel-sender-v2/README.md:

# pegel-sender-v2 — kompakte Trägerplatine mit Li-Ionen-Akku

Nachfolger von [`pegel-sender`](../pegel-sender/README.md) (bleibt für bestehende Stationen). 70 × 40 mm, 2 Lagen, alle SMD-Teile Basic oder Preferred bei JLCPCB (kein Extended), Anschlüsse als 2,54-mm-Löcher.

| | v1 | v2 |
|---|---|---|
| Akku | LiFePO4 1S, eigener Lader (TPS5430, 0,5 A) | Li-Ionen 1S am Lader des XIAO (BQ25101, 100 mA) |
| Eingang | Solarpanel 12-V-Klasse oder 12-V-Netzteil | 5 V: USB-C-Netzteil oder USB-C-Solarpanel (1–2 W reichen, `verify/winter_liion.py`) |
| Frostschutz | LM324 + NTC, Heizwiderstand extern | LM393 + NTC, Heizung aus 6 × 300 Ω auf der Platine (0,5 W) |
| Anschlüsse | Schraubklemmen | 2,54-mm-Löcher |
| Größe | 100 × 70 mm | 70 × 40 mm |

**Gleiche Firmware:** XIAO-Pins wie v1 (D0 Sonde, D6/D7 RS485, Wio-SX1262 auf D1–D5/D8–D10). Die Firmware erkennt den Li-Ionen-Akku an der Spannung am BAT-Pin des XIAO und nimmt dann die Li-Ionen-Schwellen.

## Schaltung

| Block | Bauteile | Funktion |
|---|---|---|
| Eingang | J1, Q1 AO3401A, D1 SMAJ5.0A | Verpolschutz ohne Spannungsverlust, Überspannung |
| Frost/Hitze | U1 LM393, NTC an J4, R1–R9 | Unter ~2 °C Laden aus und Heizung an, über ~43 °C Laden aus; ~1 K Hysterese; ohne NTC: kein Laden, Heizung an |
| Laden | Q2 AO3401A, Q3, D2/D3, R10/R11 | schaltet 5 V an den 5V-Pin des XIAO (dessen Lader) nur zwischen den Schwellen |
| Heizung | Q4, R12–R17 300 Ω 1206 | 0,5 W nur aus dem 5-V-Eingang, nachts nie aus dem Akku |
| Akku | J2 (Akku), J7 (Drähte zu BAT+/BAT− auf der Unterseite des XIAO) | Akku mit eigener Schutzschaltung verwenden |
| Sonde 12 V | U2 TPS61040, L1 10 µH, Q5/Q6 | wie v1, aus dem Akku |
| RS485 | U3 SP3485, Q7, Q8 | wie v1 |

**Aufbau:** Akku auf der Unterseite unter die Heizwiderstände kleben (Wärmeleitpad), den bedrahteten NTC (10 kΩ, B3950) an den Akku. Gehäuse mit ~3 cm Dämmung um Akku und Platine.

## Erzeugen

Wie v1 (KiCad 10, Java, Freerouting in `build/freerouting.jar`): `python relayout.py`. Anschlüsse, XIAO-Buchsen, Spule und Bohrungen liegen fest in `fixed_positions.py`; alle anderen Teile packt `gen_pcb.auto_place` in die Bereiche der Funktionsblöcke (`GROUP_REGIONS`). Teileprüfung: `python ../pegel-sender/verify/jlc_parts.py .`

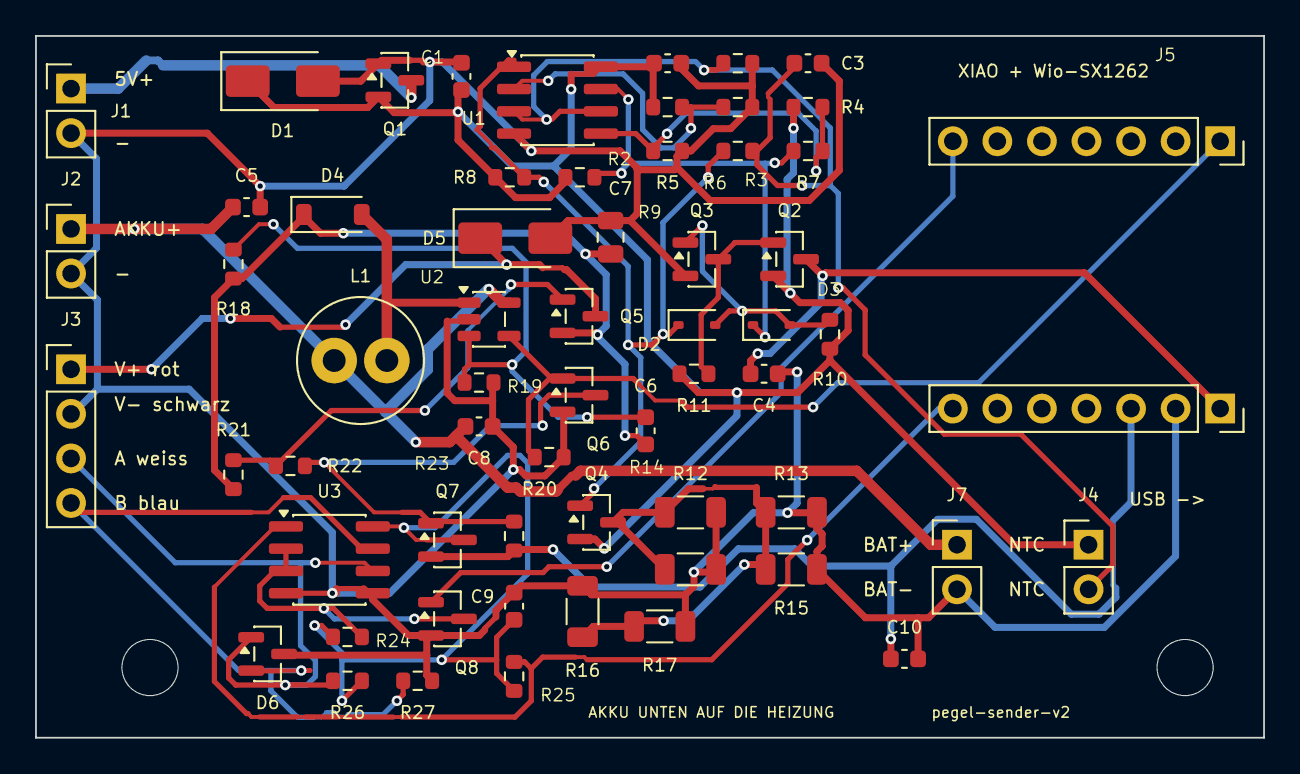
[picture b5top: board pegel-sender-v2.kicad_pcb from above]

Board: 2 copper layers, 70.0 x 40.0 mm, 64 parts (0 on the bottom side), 27 nets.

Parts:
C1, C4, C5, C8, C10: 10uF 10V; C_0603_1608Metric
C2, C3, C9: 100nF; C_0603_1608Metric
C6: 22pF; C_0603_1608Metric
C7: 10uF 25V; C_0805_2012Metric
D1: SMAJ5.0A; D_SMA
D2, D3: 1N4148WS; D_SOD-323
D4: B0540W; D_SOD-123
D5: SMAJ18A; D_SMA
D6: PSM712; SOT-23
H1, H2: M3; MountingHole_3.2mm_M3
J1: 5V IN; PinHeader_1x02_P2.54mm_Vertical
J2: AKKU Li-Ion; PinHeader_1x02_P2.54mm_Vertical
J3: SONDE; PinHeader_1x04_P2.54mm_Vertical
J4: NTC; PinHeader_1x02_P2.54mm_Vertical
J5: XIAO D0-D6; PinSocket_1x07_P2.54mm_Vertical
J6: XIAO 5V-D7; PinSocket_1x07_P2.54mm_Vertical
J7: XIAO BAT; PinHeader_1x02_P2.54mm_Vertical
L1: 10uH; L_Radial_D7.0mm_P3.00mm
Q1, Q2, Q4, Q5, Q7: AO3401A; SOT-23
Q3, Q6, Q8: 2N7002; SOT-23
R1, R3, R4, R5: 4.7k; R_0603_1608Metric
R2: 30k; R_0603_1608Metric
R6, R7: 1M; R_0603_1608Metric
R8, R9, R10, R11, R20, R21, R22, R23, R25: 100k; R_0603_1608Metric
R12, R13, R14, R15, R16, R17: 300; R_1206_3216Metric
R18: 510k; R_0603_1608Metric
R19: 56k; R_0603_1608Metric
R24, R26, R27: 10k; R_0603_1608Metric
U1: LM393; SOIC-8_3.9x4.9mm_P1.27mm
U2: TPS61040; SOT-23-5
U3: SP3485EN; SOIC-8_3.9x4.9mm_P1.27mm

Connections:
BST_FB: C6.2, R18.2, R19.1, U2.3
BST_SW: D4.2, L1.2, U2.1
CHG_EN: D2.2, D3.2, Q3.1, R10.2
CHG_G: Q2.1, Q3.3, R11.2
COLD_N: D2.1, Q4.1, R6.1, R8.2, U1.1
GND: C1.2, C2.2, C3.2, C4.2, C5.2, C7.2, C8.2, C9.2, C10.2, D1.2, D5.2, D6.3, J1.2, J2.2, J3.2, J6.2, J7.2, Q1.1, Q3.2, Q6.2, Q8.2, R1.2, R3.2, R5.2, R12.2, R13.2, R14.2, R15.2, R16.2, R17.2, R19.2, R20.2, R27.2, U1.4, U2.2, U3.4, U3.5
HEAT: Q4.3, R12.1, R13.1, R14.1, R15.1, R16.1, R17.1
HOT_N: D3.1, R7.1, R9.2, U1.7
PSW_G: Q5.1, R21.2, R22.1
PSW_PD: Q6.3, Q7.1, R22.2, R23.2
RS485_A: D6.1, J3.3, R26.1, U3.6
RS485_B: D6.2, J3.4, R27.1, U3.7
RS_DE: Q8.3, R24.2, U3.2, U3.3
RS_VCC: C9.1, Q7.3, R24.1, R25.1, R26.2, U3.8
SENS_EN: J5.1, Q6.1, R20.1, U2.4
T_COLD: R2.2, R3.1, U1.2
T_HOT: R4.2, R5.1, R7.2, U1.5
T_NTC: C3.1, J4.2, R1.1, R6.2, U1.3, U1.6
UART_RX: J6.7, R25.2, U3.1
UART_TX: J5.7, Q8.1
V5: C1.1, C2.1, D1.1, J4.1, Q1.2, Q2.2, Q4.2, R2.1, R4.1, R8.1, R9.1, R10.1, R11.1, U1.8
V12_PROBE: D5.1, J3.1, Q5.3
V12_RAW: C6.1, C7.1, D4.1, Q5.2, R18.1, R21.1
VBAT: C5.1, C8.1, J2.1, J7.1, L1.1, U2.5
VIN_RAW: J1.1, Q1.3
XIAO_3V3: C10.1, J6.3, Q7.2, R23.1
XIAO_5V: C4.1, J6.1, Q2.3

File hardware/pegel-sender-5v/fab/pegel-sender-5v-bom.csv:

Comment,Designator,Footprint,LCSC Part #
AO3401A,"Q1,Q2,Q4,Q5,Q7",SOT-23,C15127
SMAJ5.0A,D1,D_SMA,C19077523
10uF 10V,"C1,C4,C5,C8,C10",C_0603_1608Metric,C19702
LM393,U1,SOIC-8_3.9x4.9mm_P1.27mm,C7955
100nF,"C2,C3,C9",C_0603_1608Metric,C14663
4.7k,"R1,R3,R4,R5",R_0603_1608Metric,C23162
30k,R2,R_0603_1608Metric,C22984
1M,"R6,R7",R_0603_1608Metric,C22935
100k,"R8,R9,R10,R11,R20,R21,R22,R23,R25",R_0603_1608Metric,C25803
1N4148WS,"D2,D3",D_SOD-323,C2128
2N7002,"Q3,Q6,Q8",SOT-23,C8545
300,"R12,R13,R14,R15,R16,R17",R_1206_3216Metric,C17887
TPS61040,U2,SOT-23-5,C7722
B0540W,D4,D_SOD-123,C7420325
510k,R18,R_0603_1608Metric,C23192
56k,R19,R_0603_1608Metric,C23206
22pF,C6,C_0603_1608Metric,C1653
10uF 25V,C7,C_0805_2012Metric,C15850
SMAJ18A,D5,D_SMA,C19077538
SP3485EN,U3,SOIC-8_3.9x4.9mm_P1.27mm,C8963
10k,"R24,R26,R27",R_0603_1608Metric,C25804
PSM712,D6,SOT-23,C32677
